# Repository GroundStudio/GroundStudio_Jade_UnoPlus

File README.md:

GroundStudio
====================================

Get it from [ardushop.ro](https://ardushop.ro/ro/)

Explore all the GroundStudio products at [GroundStudio.ro](https://groundstudio.ro/)

Description
-------------------
Short description of the board.

Contents
-------------------

* [/Documentation](https://github.com/GroundStudio/GroundStudio_Jade_UnoPlus/tree/main/Documentation) -- Contains documentation written during creation of this repository, with readme.md index of its own!
* [/Firmware](https://github.com/GroundStudio/GroundStudio_Jade_UnoPlus/tree/main/Firmware) -- Firmware (bootloaders, etc)
* [/Hardware](https://github.com/GroundStudio/GroundStudio_Jade_UnoPlus/tree/main/Hardware) -- Schematics, layout.
* [/Libraries](https://github.com/GroundStudio/GroundStudio_Jade_UnoPlus/tree/main/Libraries) -- Arduino/CircuitPython libraries. 
* [/Tools](https://github.com/GroundStudio) -- Tools needed for compiling, uploading bootloader, etc.

Versions
-------------------
*(Not all tags shown)*
* [V1.0.0] Initial version

License
-------------------

This is released under the [Attribution-ShareAlike 4.0 International (CC BY-SA 4.0)](https://creativecommons.org/licenses/by-sa/4.0/) license. 
**You are welcome to use this library for commercial purposes.**

Please consider contributing back to this library or others to help the open-source hardware community continue to thrive and grow!

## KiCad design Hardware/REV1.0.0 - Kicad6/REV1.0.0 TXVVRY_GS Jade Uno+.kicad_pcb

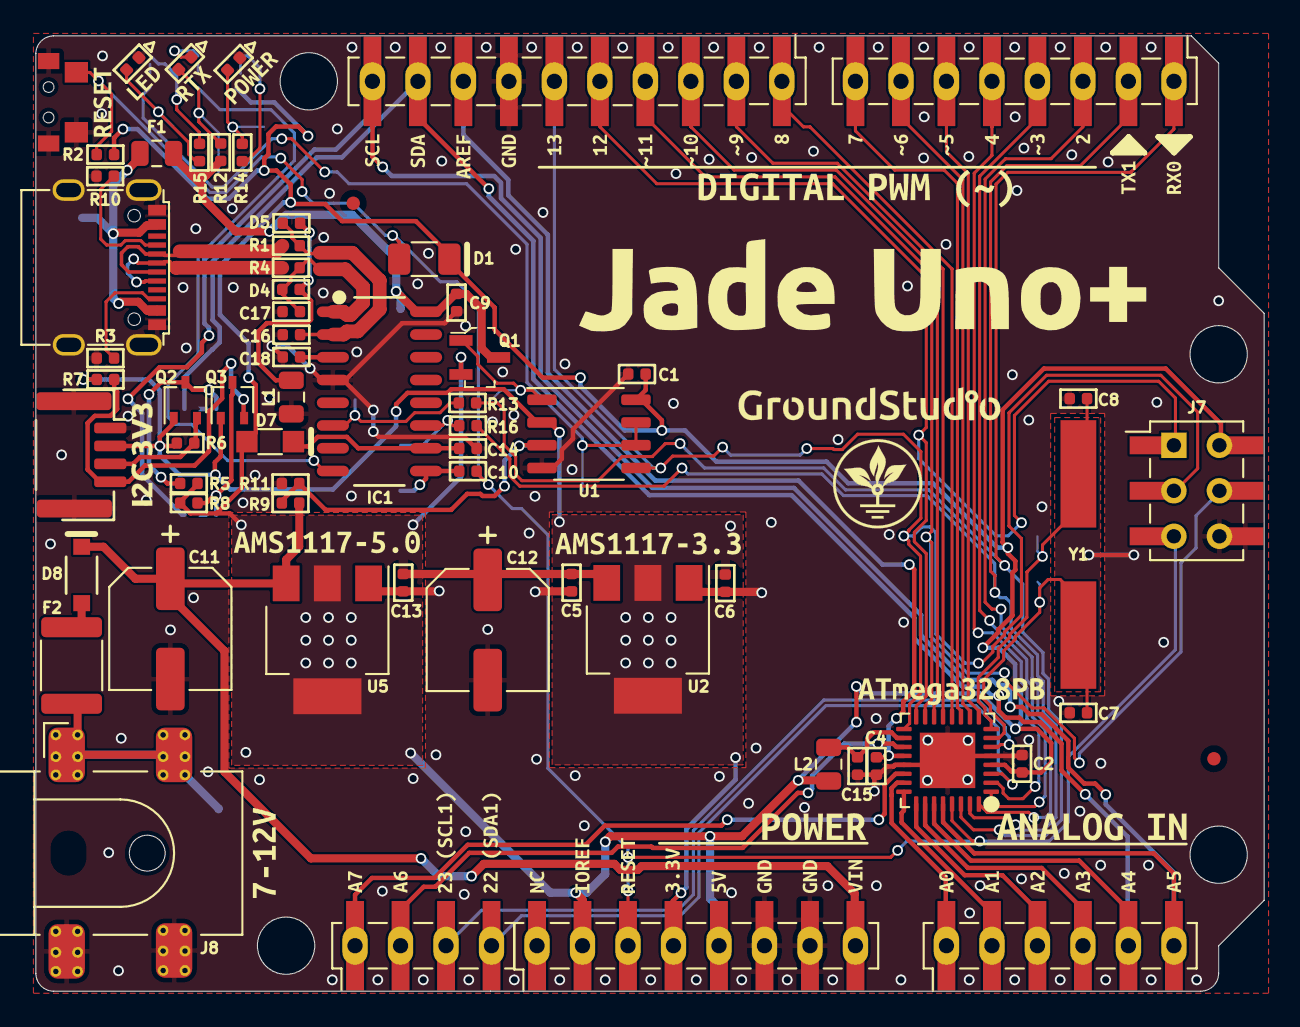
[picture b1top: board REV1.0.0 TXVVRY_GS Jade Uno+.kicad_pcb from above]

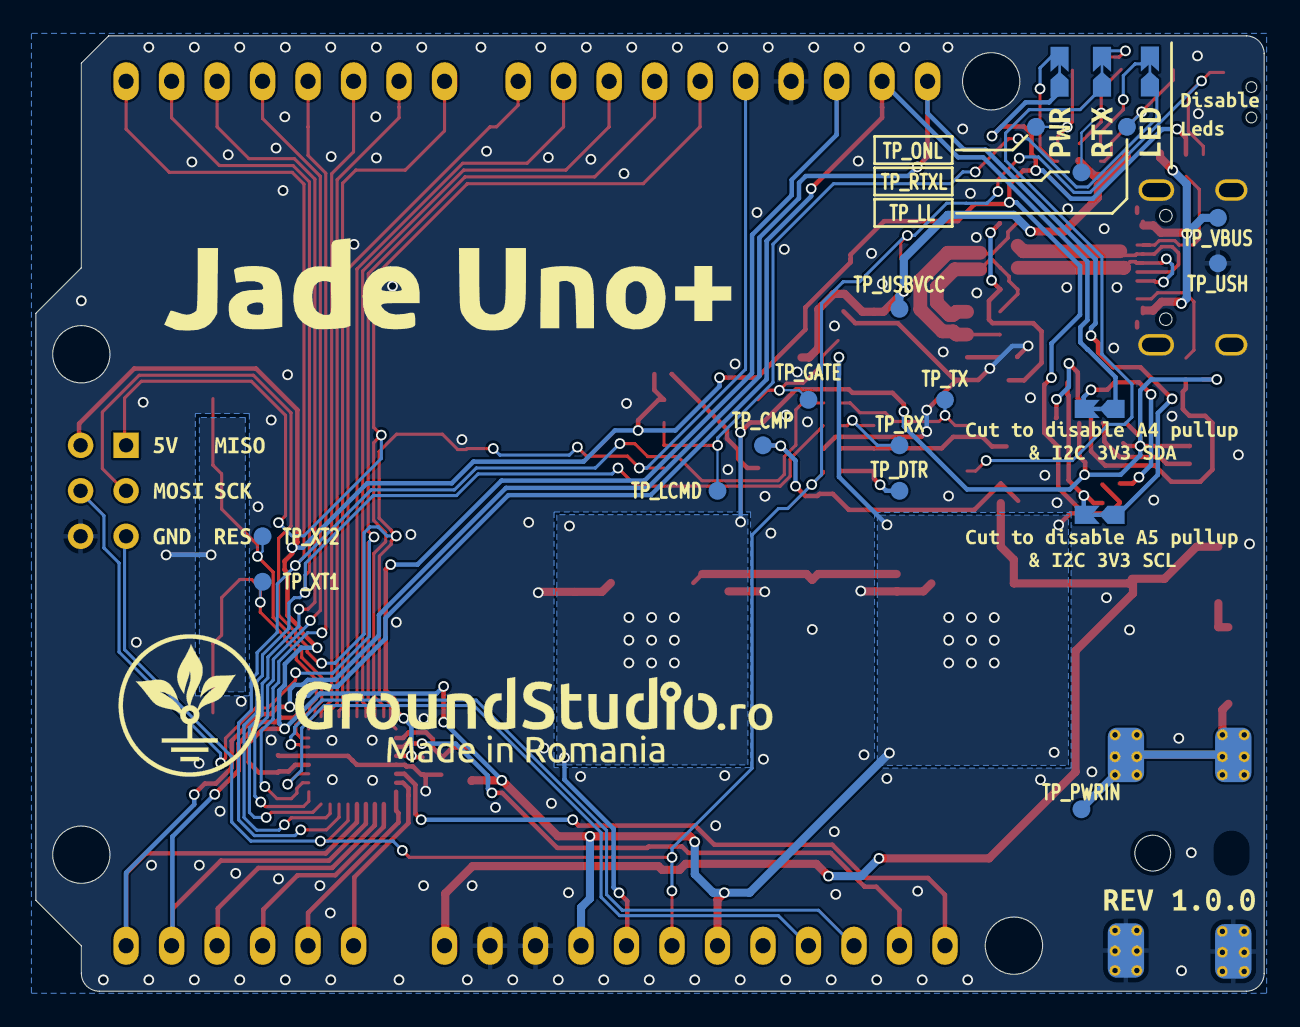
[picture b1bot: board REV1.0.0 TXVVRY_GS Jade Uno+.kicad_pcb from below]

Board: 2 copper layers, 68.6 x 53.3 mm, 148 parts (20 on the bottom side), 63 nets.

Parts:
C1, C2, C4, C9, C10, C13, C14, C15: C_0402_100nF_16V; C_0402
C5, C6: C_0402_10uF_10V; C_0402
C7, C8: C_0402_22pF_50V; C_0402
C11, C12: CP_Elec_6.3x5.4_47uF_25V; CP_Elec_6.3x5.4
C16, C17: C_0402_47pF_50V; C_0402
C18: C_0402_1uF_10V; C_0402
D1: D_1206_CD1206-S01575; D_1206
D2, D6: LED_0402_GREEN; LED_0402
D3: LED_0402_RED; LED_0402
D4, D5: R_0402_PS0402V014AT; R_0402
D7: SOD-323 SD103AWS; SOD-323
D8: SOD-123 1N4007W; SOD-123
F1: Fuse_0805_MF-PSMF050X-2; R_0805
F2: Fuse_1812_MF-MSMF050-2; Fuse_1812
FID1, FID2: Fiducial; Fiducial_0.75mm_Mask1.5mm
IC1: SOP-16_150MIL HT42B534-2; SOP-16_150MIL
J1, J9: SolderJumper_NC; SolderJumper_NC_0.65-A_1Oz_OuterLayer_5C-T
J2: SH_1x04_P1.0_H; SH__1x04_P1.00mm_Horizontal
J3: PinH_1x10_P2.54_V_F_SMD; PinHeader_1x10_P2.54_V_F_SMD+THT
J4, J5: PinH_1x8_P2.54_V_F_SMD; PinHeader_1x8_P2.54_V_F_SMD+THT
J6: PinH_1x6_P2.54_V_F_SMD; PinHeader_1x6_P2.54_V_F_SMD+THT
J7: PinHeader_2x03_P2.54_V_M; PinSocket_2x03_P2.54_V_F_SMD+THT
J8: DC-005-5.5-Barr_Jck_SMD; DC-005-5.5-2.0MM-SMD
J10: Conn_01x04; PinHeader_1x04_P2.54_V_F_SMD+THT
J12, J13, J14: SolderJumper_NC
L1: L_0805_BLM21PG221SN1D; L_0805
L2: L_0805_SCMI201209X100KT; L_0805
Q1: SOT-23 IRLML6402; SOT-23-3
Q2, Q3: SOT-323 2N7002PW; SOT-323_SC-70
R1, R4: R_0402_33; R_0402
R2, R9, R11: R_0402_10k; R_0402
R3, R10: R_0402_5.1k; R_0402
R5, R6, R7, R8: R_0402_2.2k; R_0402
R12, R14, R15: R_0402_20k; R_0402
R13, R16: R_0402_1k; R_0402
SW2: TS24CA
TP1: TP_VBUS; TestPoint
TP2: TP_USBVCC; TestPoint
TP3: TP_LCMD; TestPoint
TP4: TP_USH; TestPoint
TP5: TP_GATE; TestPoint
TP6: TP_CMP; TestPoint
TP7: TP_TX; TestPoint
TP8: TP_LL; TestPoint
TP9: TP_RX; TestPoint
TP10: TP_ONL; TestPoint
TP13: TP_RTXL; TestPoint
TP16: TP_XT1; TestPoint
TP18: TP_XT2; TestPoint
TP19: TP_DTR; TestPoint
TP23: TP_PWRIN; TestPoint
U1: SOP-8_3.9x4.9_P1.27 LM358; SOP-8_3.9x4.9mm_P1.27mm
U2: SOT-223 AMS1117-3.3; SOT-223
U3: ATmega328PB-MUR; QFN-32-1EP_5x5_P0.5_EP3.1x3.1
U5: SOT-223 AMS1117-5.0; SOT-223
USB1: USB_C_FULL; USB_C_C167321
Y1: HC49-SMD 5M0-1600A2020; Crystal_HC49-SMD
kibuzzard-6304B8AA: G***; kibuzzard-6304B8AA
kibuzzard-6304B8C4: G***; kibuzzard-6304B8C4
kibuzzard-6304B90F: G***; kibuzzard-6304B90F
kibuzzard-6304B959: G***; kibuzzard-6304B959
kibuzzard-6304BA0A: G***; kibuzzard-6304BA0A
kibuzzard-6304BA95: G***; kibuzzard-6304BA95
kibuzzard-6304BB5A: G***; kibuzzard-6304BB5A
kibuzzard-6304BB7B: G***; kibuzzard-6304BB7B
kibuzzard-6304BB25: G***; kibuzzard-6304BB25
kibuzzard-6304BB68: G***; kibuzzard-6304BB68
kibuzzard-6304BC48: G***; kibuzzard-6304BC48
kibuzzard-6304BC55: G***; kibuzzard-6304BC55
kibuzzard-6304BC77: G***; kibuzzard-6304BC77
kibuzzard-6304BD32: G***; kibuzzard-6304BD32
kibuzzard-6304BD56: G***; kibuzzard-6304BD56
kibuzzard-6304BD88: G***; kibuzzard-6304BD88
kibuzzard-6304BDD1: G***; kibuzzard-6304BDD1
kibuzzard-6304BDFC: G***; kibuzzard-6304BDFC
kibuzzard-6304BE0A: G***; kibuzzard-6304BE0A
kibuzzard-6304BE24, kibuzzard-6304BE24#2, kibuzzard-6304BE24#3: G***; kibuzzard-6304BE24
kibuzzard-6304BE44: G***; kibuzzard-6304BE44
kibuzzard-6304BE81: G***; kibuzzard-6304BE81
kibuzzard-6304BEA3: G***; kibuzzard-6304BEA3
kibuzzard-6304BEBA: G***; kibuzzard-6304BEBA
kibuzzard-6304BEF7: G***; kibuzzard-6304BEF7
kibuzzard-6304BF4E: G***; kibuzzard-6304BF4E
kibuzzard-6304BF08: G***; kibuzzard-6304BF08
kibuzzard-6304BF17: G***; kibuzzard-6304BF17
kibuzzard-6304BF64: G***; kibuzzard-6304BF64
kibuzzard-6304BF84: G***; kibuzzard-6304BF84
kibuzzard-6304BFA8: G***; kibuzzard-6304BFA8
kibuzzard-6304BFB9: G***; kibuzzard-6304BFB9
kibuzzard-6304BFCD: G***; kibuzzard-6304BFCD
kibuzzard-6304BFE9: G***; kibuzzard-6304BFE9
kibuzzard-6304BFFA: G***; kibuzzard-6304BFFA
kibuzzard-6304C1E0: G***; kibuzzard-6304C1E0
kibuzzard-6304C1FC: G***; kibuzzard-6304C1FC
kibuzzard-6304C4A6: G***; kibuzzard-6304C4A6
kibuzzard-6304C4B7: G***; kibuzzard-6304C4B7
kibuzzard-6304C4F3: G***; kibuzzard-6304C4F3
kibuzzard-6304C05A: G***; kibuzzard-6304C05A
kibuzzard-6304C6B6: G***; kibuzzard-6304C6B6
kibuzzard-6304C016: G***; kibuzzard-6304C016
kibuzzard-6304C31B: G***; kibuzzard-6304C31B
kibuzzard-6304C044: G***; kibuzzard-6304C044
kibuzzard-6304C46A: G***; kibuzzard-6304C46A
kibuzzard-6304C47B: G***; kibuzzard-6304C47B
kibuzzard-6304C185: G***; kibuzzard-6304C185
kibuzzard-6304C295: G***; kibuzzard-6304C295
kibuzzard-6304C450: G***; kibuzzard-6304C450
kibuzzard-6304C490: G***; kibuzzard-6304C490
kibuzzard-6304C525: G***; kibuzzard-6304C525
kibuzzard-6304C555: G***; kibuzzard-6304C555
kibuzzard-6304C570: G***; kibuzzard-6304C570
kibuzzard-6304D41D: G***; kibuzzard-6304D41D
kibuzzard-6304D43B: G***; kibuzzard-6304D43B
kibuzzard-6304D472: G***; kibuzzard-6304D472
kibuzzard-632175D7: G***; kibuzzard-632175D7
kibuzzard-63208071: G***; kibuzzard-63208071
kibuzzard-63217612: G***; kibuzzard-63217612

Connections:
+3V3: C6.1, J2.2 (3V3), J5.4, Q2.1 (G), Q3.1 (G), R6.1, R7.1, U1.2, U2.2 (VO), U2.4
+5V: C1.1, C2.1, C5.1, C12.1, C13.1, D1.1 (K), D7.2 (A), J5.2, J5.5, J7.2, J13.1, L2.1, Q1.2 (S), R2.2, R5.2, R8.2, U1.8 (VCC), U2.3 (VI), U3.4 (VCC), U5.2 (VO), U5.4
A0: J6.1, U3.23 (PC0)
A1: J6.2, U3.24 (PC1)
A2: J6.3, U3.25 (PC2)
A3: J6.4, U3.26 (PC3)
A4_SDA: J3.9, J6.5, J9.1, U3.27 (PC4)
A5_SCL: J1.1, J3.10, J6.6, U3.28 (PC5)
ADC6/PE2: J10.2, U3.19 (ADC6/PE2)
ADC7/PE3: J10.1, U3.22 (ADC7/PE3)
AREF: C4.1, J3.8, U3.20 (AREF)
D2: J4.3, U3.32 (PD2)
D3: J4.4, U3.1 (PD3)
D4: J4.5, U3.2 (PD4)
D5: J4.6, U3.9 (PD5)
D6: J4.7, U3.10 (PD6)
D7: J4.8, U3.11 (PD7)
D8: J3.1, U3.12 (PB0)
D9: J3.2, U3.13 (PB1)
D10_SS: J3.3, U3.14 (PB2)
D11_MOSI: J3.4, J7.4, U3.15 (PB3)
D12_MISO: J3.5, J7.1, U3.16 (PB4)
D13_SCK: J3.6, J7.3, U1.5, U3.17 (PB5)
D+: R4.1, USB1.A6 (DP1), USB1.B6 (DP2)
D-: R1.1, USB1.A7 (DN1), USB1.B7 (DN2)
GND: C1.2, C2.2, C4.2, C5.2, C6.2, C7.1, C8.1, C9.2, C11.2, C12.2, C13.2, C14.2, C15.2, C16.1, C17.1, C18.2, D2.1 (K), D3.1 (K), IC1.4 (GND), J2.0 (SHIELD), J2.1 (GND), J3.7, J5.6, J5.7, J7.6, J8.3, J8.4, L1.2, R3.1, R10.2, R11.1, SW2.1, SW2.2, SW2.3, TP4.1, U1.4 (GND), U2.1 (GND), U3.5 (GND), U3.21 (GND), U3.33 (GND), U5.1 (GND), USB1.0 (SHLD), USB1.A1 (GND), USB1.A12 (GND), USB1.B1 (GND), USB1.B12 (GND)
IC1_RX: IC1.11 (RX), R16.2, TP9.1
IC1_TX: IC1.6 (TX), R13.2, TP7.1
L_CMD: J14.1, TP3.1, U1.6, U1.7
unnamed: C7.2, TP16.1, U3.7 (XTAL1/PB6), Y1.1
unnamed: C8.2, TP18.1, U3.8 (XTAL2/PB7), Y1.2
unnamed: C10.1, IC1.9 (~DTR), TP19.1
unnamed: C14.1, D7.1 (K), IC1.10 (VDDIO)
unnamed: C15.1, L2.2, U3.18 (AVCC)
unnamed: C18.1, IC1.3 (V33O)
unnamed: D2.2 (A), R15.2, TP8.1
unnamed: D3.2 (A), R14.2, TP10.1
unnamed: D4.1, D5.2, L1.1
unnamed: D6.1 (K), J12.2
unnamed: D6.2 (A), R12.1, TP13.1
unnamed: D8.2 (A), F2.1
unnamed: F2.2, J8.5, TP23.1
unnamed: IC1.8 (LED), J12.1
unnamed: J1.2, Q3.3 (D), R8.1
unnamed: J2.3 (SDA), Q2.2 (S), R6.2
unnamed: J2.4 (SCL), Q3.2 (S), R7.2
unnamed: J9.2, Q2.3 (D), R5.1
unnamed: J13.2, R14.1
unnamed: J14.2, R15.1
unnamed: Q1.1 (G), TP5.1, U1.1
unnamed: R3.2, USB1.B5 (CC2)
unnamed: R10.1, USB1.A5 (CC1)
unnamed: R9.1, R11.2, TP6.1, U1.3
PE0: J10.4, U3.3 (PE0/ACO)
PE1: J10.3, U3.6 (PE[1])
RES: C10.2, D1.2 (A), J5.3, J7.5, R2.1, SW2.4, U3.29 (~RESET/PC6)
RX0: J4.1, R13.1, U3.30 (PD0)
TX1: J4.2, R16.1, U3.31 (PD1)
UD+: C17.2, D4.2, IC1.1 (D+), R4.2
UD-: C16.2, D5.1, IC1.2 (D-), R1.2
USB_VCC: C9.1, F1.1, IC1.16 (VDD), Q1.3 (D), R12.2, TP2.1
VBUS: F1.2, TP1.1, USB1.A4 (VBUS), USB1.A9 (VBUS), USB1.B4 (VBUS), USB1.B9 (VBUS)
VIN: C11.1, D8.1 (K), J5.8, R9.2, U5.3 (VI)

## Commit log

2023-03-15 Update README.md
    - removed references to "library"
2023-10-26 - added .step 3D file of the board
